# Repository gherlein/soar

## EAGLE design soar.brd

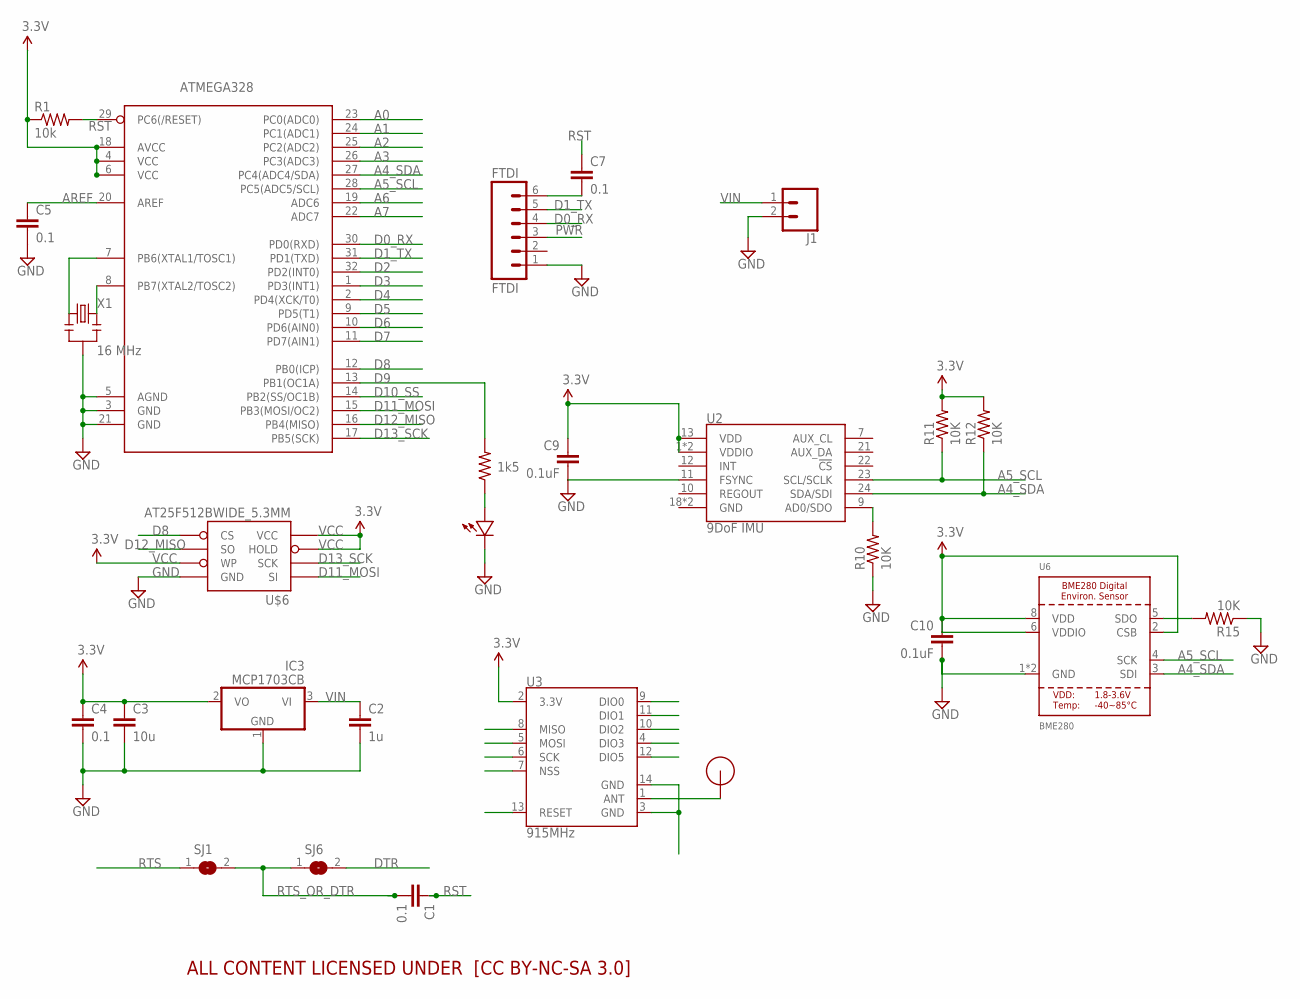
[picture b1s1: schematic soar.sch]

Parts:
ATMEGA328: ATMega-328; TQFP32-08
C1, C4, C5, C7: 0.1; 0603-CAP
C2: 1u; 0603-CAP
C3: 10u; 0805-CAP
C9, C10: 0.1uF; 0603-CAP
FTDI: FTDI; 1X06
IC3: MCP1703CB; SOT23
J1: CONN_02-JST-2-PTH-NO_SILK; JST-2-PTH-NS
R1: 10k; 0603-RES
R2: 1k5; 0603-RES
R10, R11, R12, R15: 10K; 0603-RES
SJ1, SJ6: JUMPER; SJW
U2: 9DoF IMU; QFN24-3X3
U3: 915MHz; RFM69CW-XXXS2
U6: BME280
U$2: LED0603; 0603-LED
U$3: RFM12B_ANTENNA; RFM12B-ANTENNA
U$6: AT25F512BWIDE_5.3MM; SO08WIDE
X1: 16 MHz; RESONATOR-SMD

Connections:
A0: ATMEGA328.23 (PC0(ADC0))
A1: ATMEGA328.24 (PC1(ADC1))
A2: ATMEGA328.25 (PC2(ADC2))
A3: ATMEGA328.26 (PC3(ADC3))
A4_SDA: ATMEGA328.27 (PC4(ADC4/SDA)), R12.1, U2.24 (SDA/SDI), U6.3 (SDI)
A5_SCL: ATMEGA328.28 (PC5(ADC5/SCL)), R11.1, U2.23 (SCL/SCLK), U6.4 (SCK)
A6: ATMEGA328.19 (ADC6)
A7: ATMEGA328.22 (ADC7)
AREF: ATMEGA328.20 (AREF), C5.1
D0_RX: ATMEGA328.30 (PD0(RXD)), FTDI.4
D1_TX: ATMEGA328.31 (PD1(TXD)), FTDI.5
D2: ATMEGA328.32 (PD2(INT0)), U3.9 (DIO0)
D3: ATMEGA328.1 (PD3(INT1))
D4: ATMEGA328.2 (PD4(XCK/T0))
D5: ATMEGA328.9 (PD5(T1))
D6: ATMEGA328.10 (PD6(AIN0))
D7: ATMEGA328.11 (PD7(AIN1))
D8: ATMEGA328.12 (PB0(ICP)), U$6.1 (CS)
D9: ATMEGA328.13 (PB1(OC1A)), R2.2
D10_SS: ATMEGA328.14 (PB2(SS/OC1B)), U3.7 (NSS)
D11_MOSI: ATMEGA328.15 (PB3(MOSI/OC2)), U3.5 (MOSI), U$6.5 (SI)
D12_MISO: ATMEGA328.16 (PB4(MISO)), U3.8 (MISO), U$6.2 (SO)
D13_SCK: ATMEGA328.17 (PB5(SCK)), U3.6 (SCK), U$6.6 (SCK)
DTR: SJ6.2
GND: ATMEGA328.3 (GND), ATMEGA328.5 (AGND), ATMEGA328.21 (GND), C2.2, C3.2, C4.2, C5.2, C10.2, FTDI.1, IC3.1 (GND), J1.2, R10.1, R15.1, U6.1 (GND), U6.7 (GND), U$2.MINUS, U$6.4 (GND), X1.2
unnamed: ATMEGA328.7 (PB6(XTAL1/TOSC1)), X1.1
unnamed: R2.1, U$2.PLUS
unnamed: C9.2, U2.11 (FSYNC)
unnamed: R15.2, U6.5 (SDO)
unnamed: R10.2, U2.9 (AD0/SDO)
unnamed: C7.2, FTDI.6
unnamed: U3.3 (GND), U3.14 (GND)
unnamed: ATMEGA328.8 (PB7(XTAL2/TOSC2)), X1.3
unnamed: U3.1 (ANT), U$3.P$1
PWR: FTDI.3
RST: ATMEGA328.29 (PC6(/RESET)), C1.1, C7.1, R1.2
RTS: SJ1.1
RTS_OR_DTR: C1.2, SJ1.2, SJ6.1
VCC: ATMEGA328.4 (VCC), ATMEGA328.6 (VCC), ATMEGA328.18 (AVCC), C3.1, C4.1, C9.1, C10.1, IC3.2 (VO), R1.1, R11.2, R12.2, U2.1 (VDDIO), U2.8 (VDDIO), U2.13 (VDD), U3.2 (3.3V), U6.2 (CSB), U6.6 (VDDIO), U6.8 (VDD), U$6.3 (WP), U$6.7 (HOLD), U$6.8 (VCC)
VIN: C2.1, IC3.3 (VI), J1.1

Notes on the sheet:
ALL CONTENT LICENSED UNDER [CC BY-NC-SA 3.0]

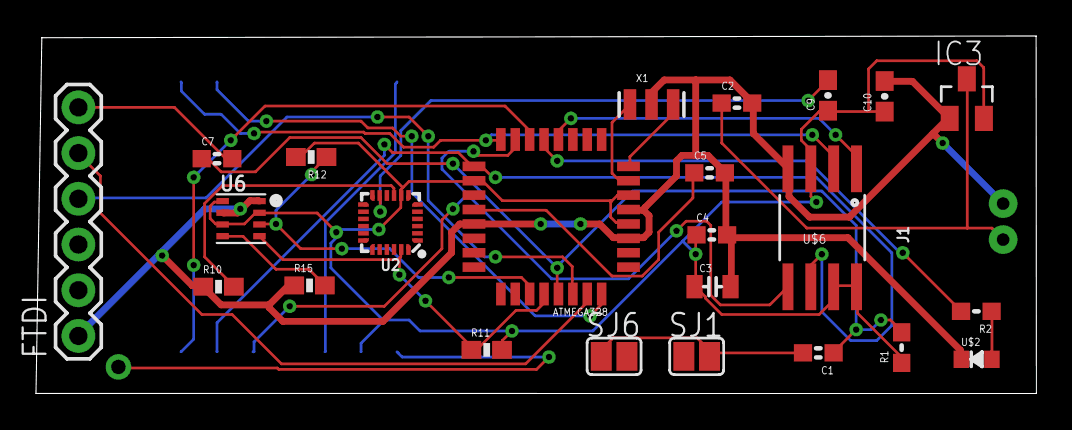
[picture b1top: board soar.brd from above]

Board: 2 copper layers, 55.6 x 19.9 mm, 27 parts (1 on the bottom side), 26 nets.

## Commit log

2017-09-11 one routeing
2017-09-17 in progress

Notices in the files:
parts and their libraries:
SparkFun-Capacitors: Licensing: Creative Commons ShareAlike 4.0 International - https://creativecommons.org/licenses/by-sa/4.0
